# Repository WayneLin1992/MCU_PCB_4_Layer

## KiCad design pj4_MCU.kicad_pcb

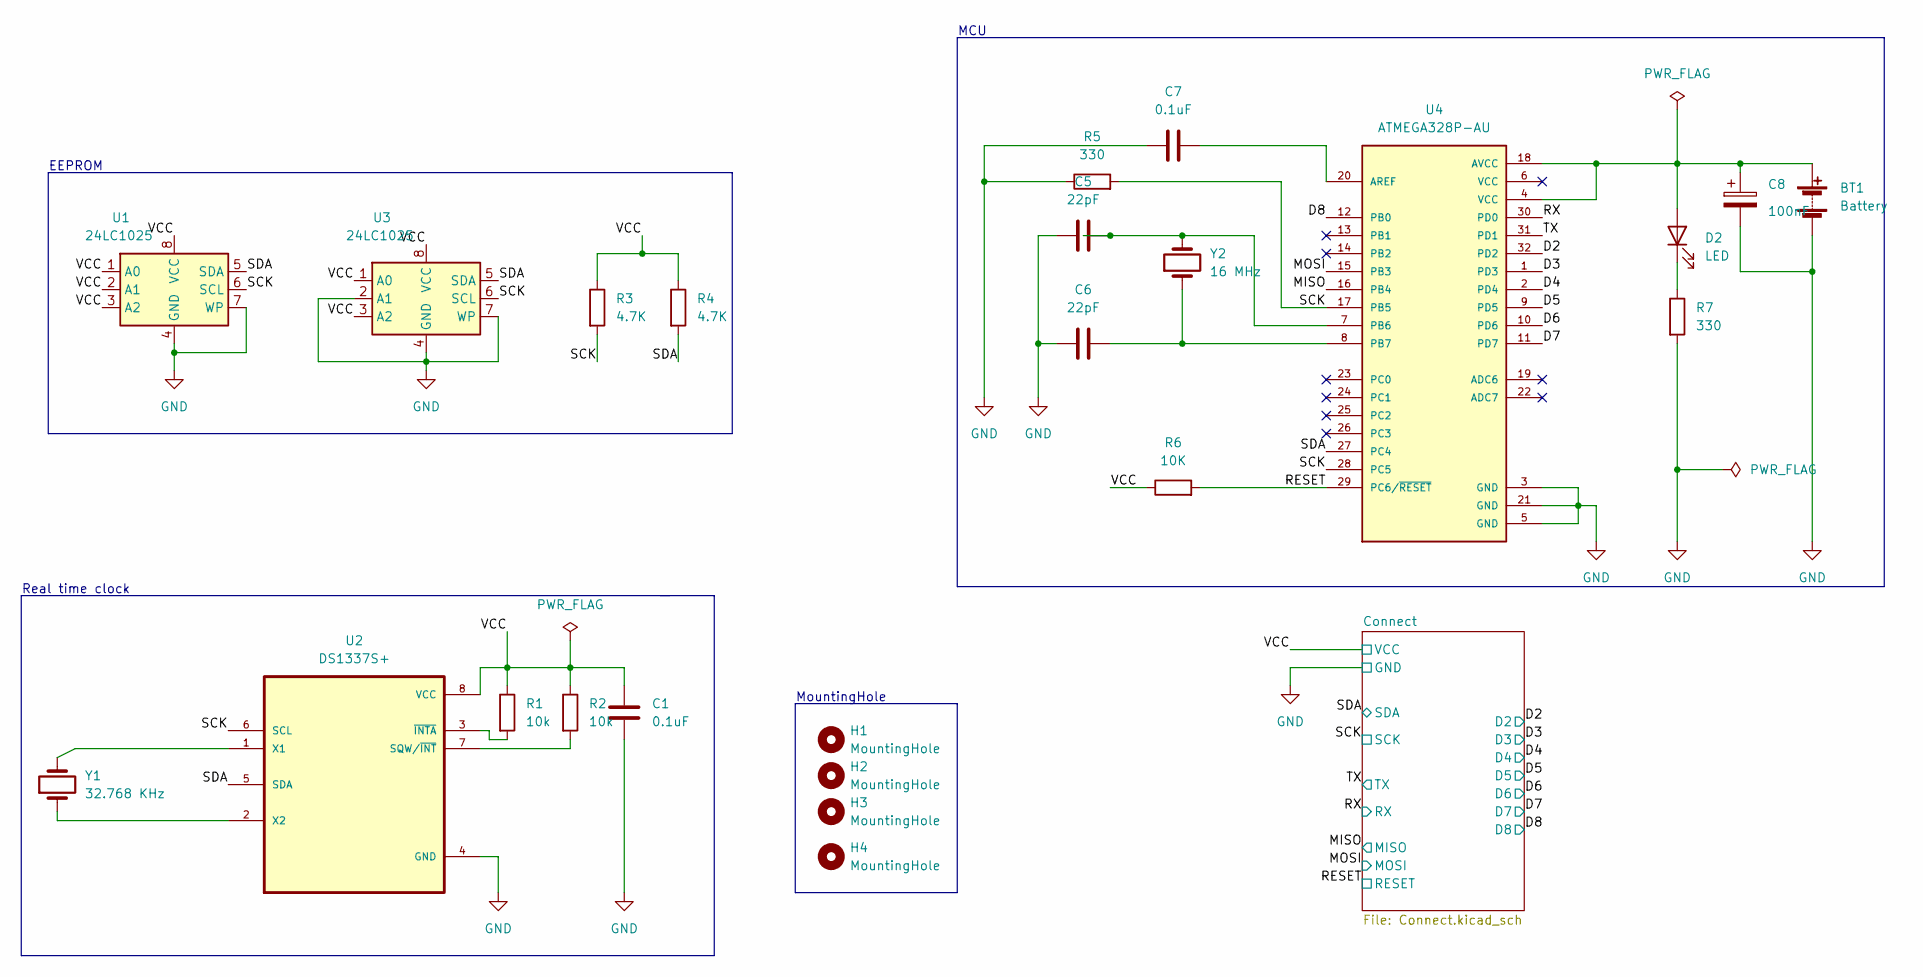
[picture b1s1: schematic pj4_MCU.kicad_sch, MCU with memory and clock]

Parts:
BT1: Battery; PinHeader_1x02_P2.54mm_Vertical
C1, C7: 0.1uF; C_0805_2012Metric
C5, C6: 22pF; C_0805_2012Metric
C8: 100nF; C_0805_2012Metric
D2: LED; LED_0805_2012Metric
H1, H2, H3, H4: MountingHole; MountingHole_2.1mm
R1, R2: 10k; R_0805_2012Metric
R3, R4: 4.7K; R_0805_2012Metric
R5, R7: 330; R_0805_2012Metric
R6: 10K; R_0805_2012Metric
U1, U3: 24LC1025; SOIC-8_3.9x4.9mm_P1.27mm
U2: DS1337S+; SOIC127P600X175-8N
U4: ATMEGA328P-AU; QFP80P900X900X120-32N
Y1: 32.768 KHz; Crystal_SMD_5032-2Pin_5.0x3.2mm_HandSoldering
Y2: 16 MHz; Crystal_SMD_5032-2Pin_5.0x3.2mm_HandSoldering

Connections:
/D2: U4.32 (PD2); also elsewhere on the board
/D3: U4.1 (PD3); also elsewhere on the board
/D4: U4.2 (PD4); also elsewhere on the board
/D5: U4.9 (PD5); also elsewhere on the board
/D6: U4.10 (PD6); also elsewhere on the board
/D7: U4.11 (PD7); also elsewhere on the board
/D8: U4.12 (PB0); also elsewhere on the board
/MISO: U4.16 (PB4); also elsewhere on the board
/MOSI: U4.15 (PB3); also elsewhere on the board
/RESET: R6.2, U4.29 (PC6/~RESET); also elsewhere on the board
/RX: U4.30 (PD0); also elsewhere on the board
/SCK: R3.2, R5.2, U1.6 (SCL), U2.6 (SCL), U3.6 (SCL), U4.17 (PB5), U4.28 (PC5); also elsewhere on the board
/SDA: R4.2, U1.5 (SDA), U2.5 (SDA), U3.5 (SDA), U4.27 (PC4); also elsewhere on the board
/TX: U4.31 (PD1); also elsewhere on the board
GND: BT1.2 (-), C1.2, C5.1, C6.2, C7.1, C8.2, R5.1, R7.2, U1.4 (GND), U1.7 (WP), U2.4 (GND), U3.2 (A1), U3.4 (GND), U3.7 (WP), U4.3 (GND), U4.5 (GND), U4.21 (GND); also elsewhere on the board
unnamed: D2.1 (K), R7.1
unnamed: U2.1 (X1), Y1.2
unnamed: U2.2 (X2), Y1.1
unnamed: R1.2, U2.3 (~INTA)
unnamed: R2.2, U2.7 (SQW/~INT)
unnamed: C5.2, U4.7 (PB6), Y2.2
unnamed: C7.2, U4.20 (AREF)
unnamed: C6.1, U4.8 (PB7), Y2.1

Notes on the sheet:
MCU
MountingHole
EEPROM
Real time clock

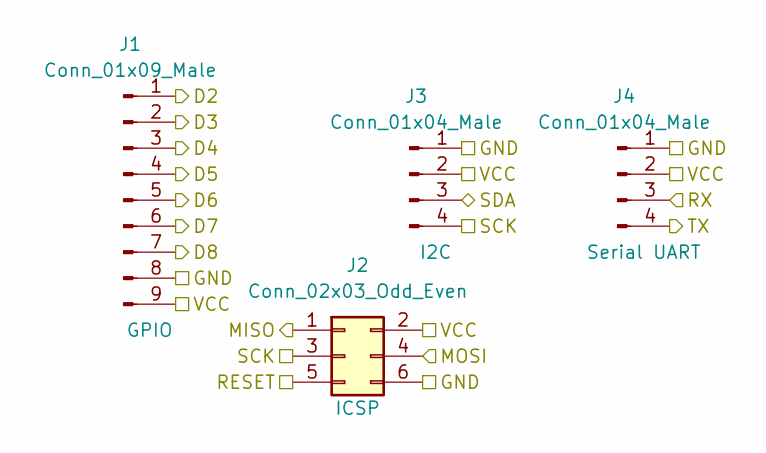
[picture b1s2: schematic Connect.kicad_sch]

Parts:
J1: Conn_01x09_Male; PinHeader_1x09_P2.54mm_Vertical
J2: Conn_02x03_Odd_Even; PinHeader_2x03_P2.54mm_Vertical
J3, J4: Conn_01x04_Male; PinHeader_1x04_P2.54mm_Vertical

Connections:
/D2: J1.1; also elsewhere on the board
/D3: J1.2; also elsewhere on the board
/D4: J1.3; also elsewhere on the board
/D5: J1.4; also elsewhere on the board
/D6: J1.5; also elsewhere on the board
/D7: J1.6; also elsewhere on the board
/D8: J1.7; also elsewhere on the board
/MISO: J2.1; also elsewhere on the board
/MOSI: J2.4; also elsewhere on the board
/RESET: J2.5; also elsewhere on the board
/RX: J4.3; also elsewhere on the board
/SCK: J2.3, J3.4; also elsewhere on the board
/SDA: J3.3; also elsewhere on the board
/TX: J4.4; also elsewhere on the board
GND: J1.8, J2.6, J3.1, J4.1; also elsewhere on the board

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
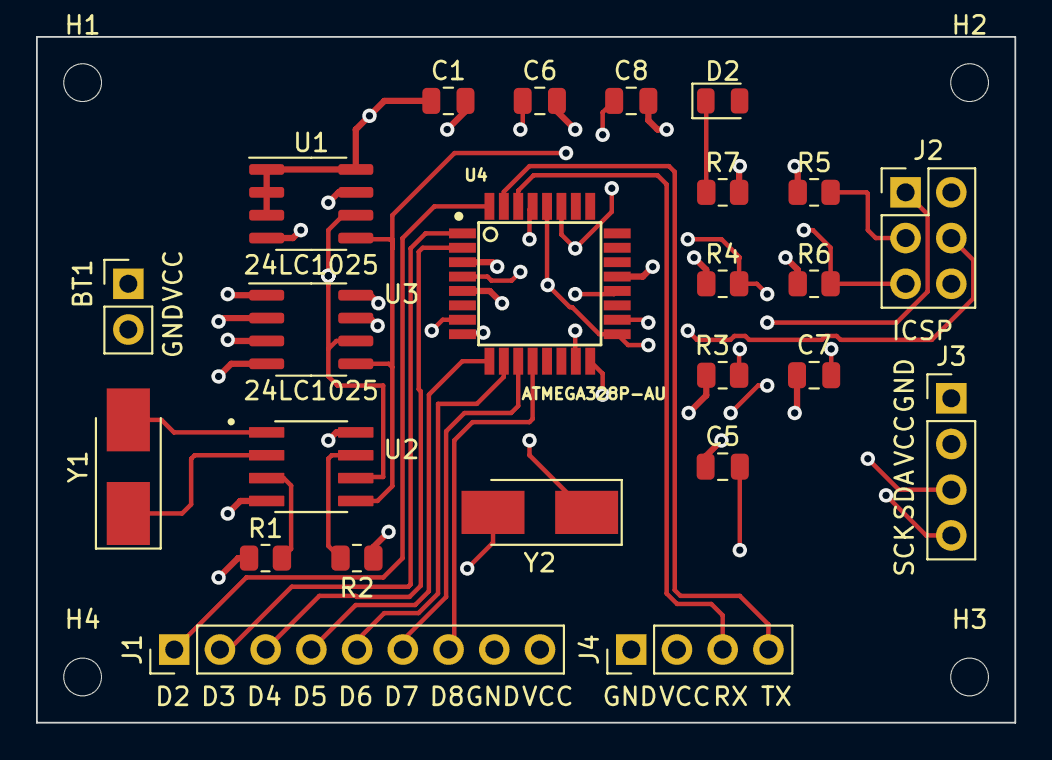
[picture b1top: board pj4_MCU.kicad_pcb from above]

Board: 4 copper layers, 54.4 x 38.1 mm, 28 parts (0 on the bottom side), 24 nets.

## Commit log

2022-01-07 4 layer MCU PCB
2022-01-09 update MCU_PCB
